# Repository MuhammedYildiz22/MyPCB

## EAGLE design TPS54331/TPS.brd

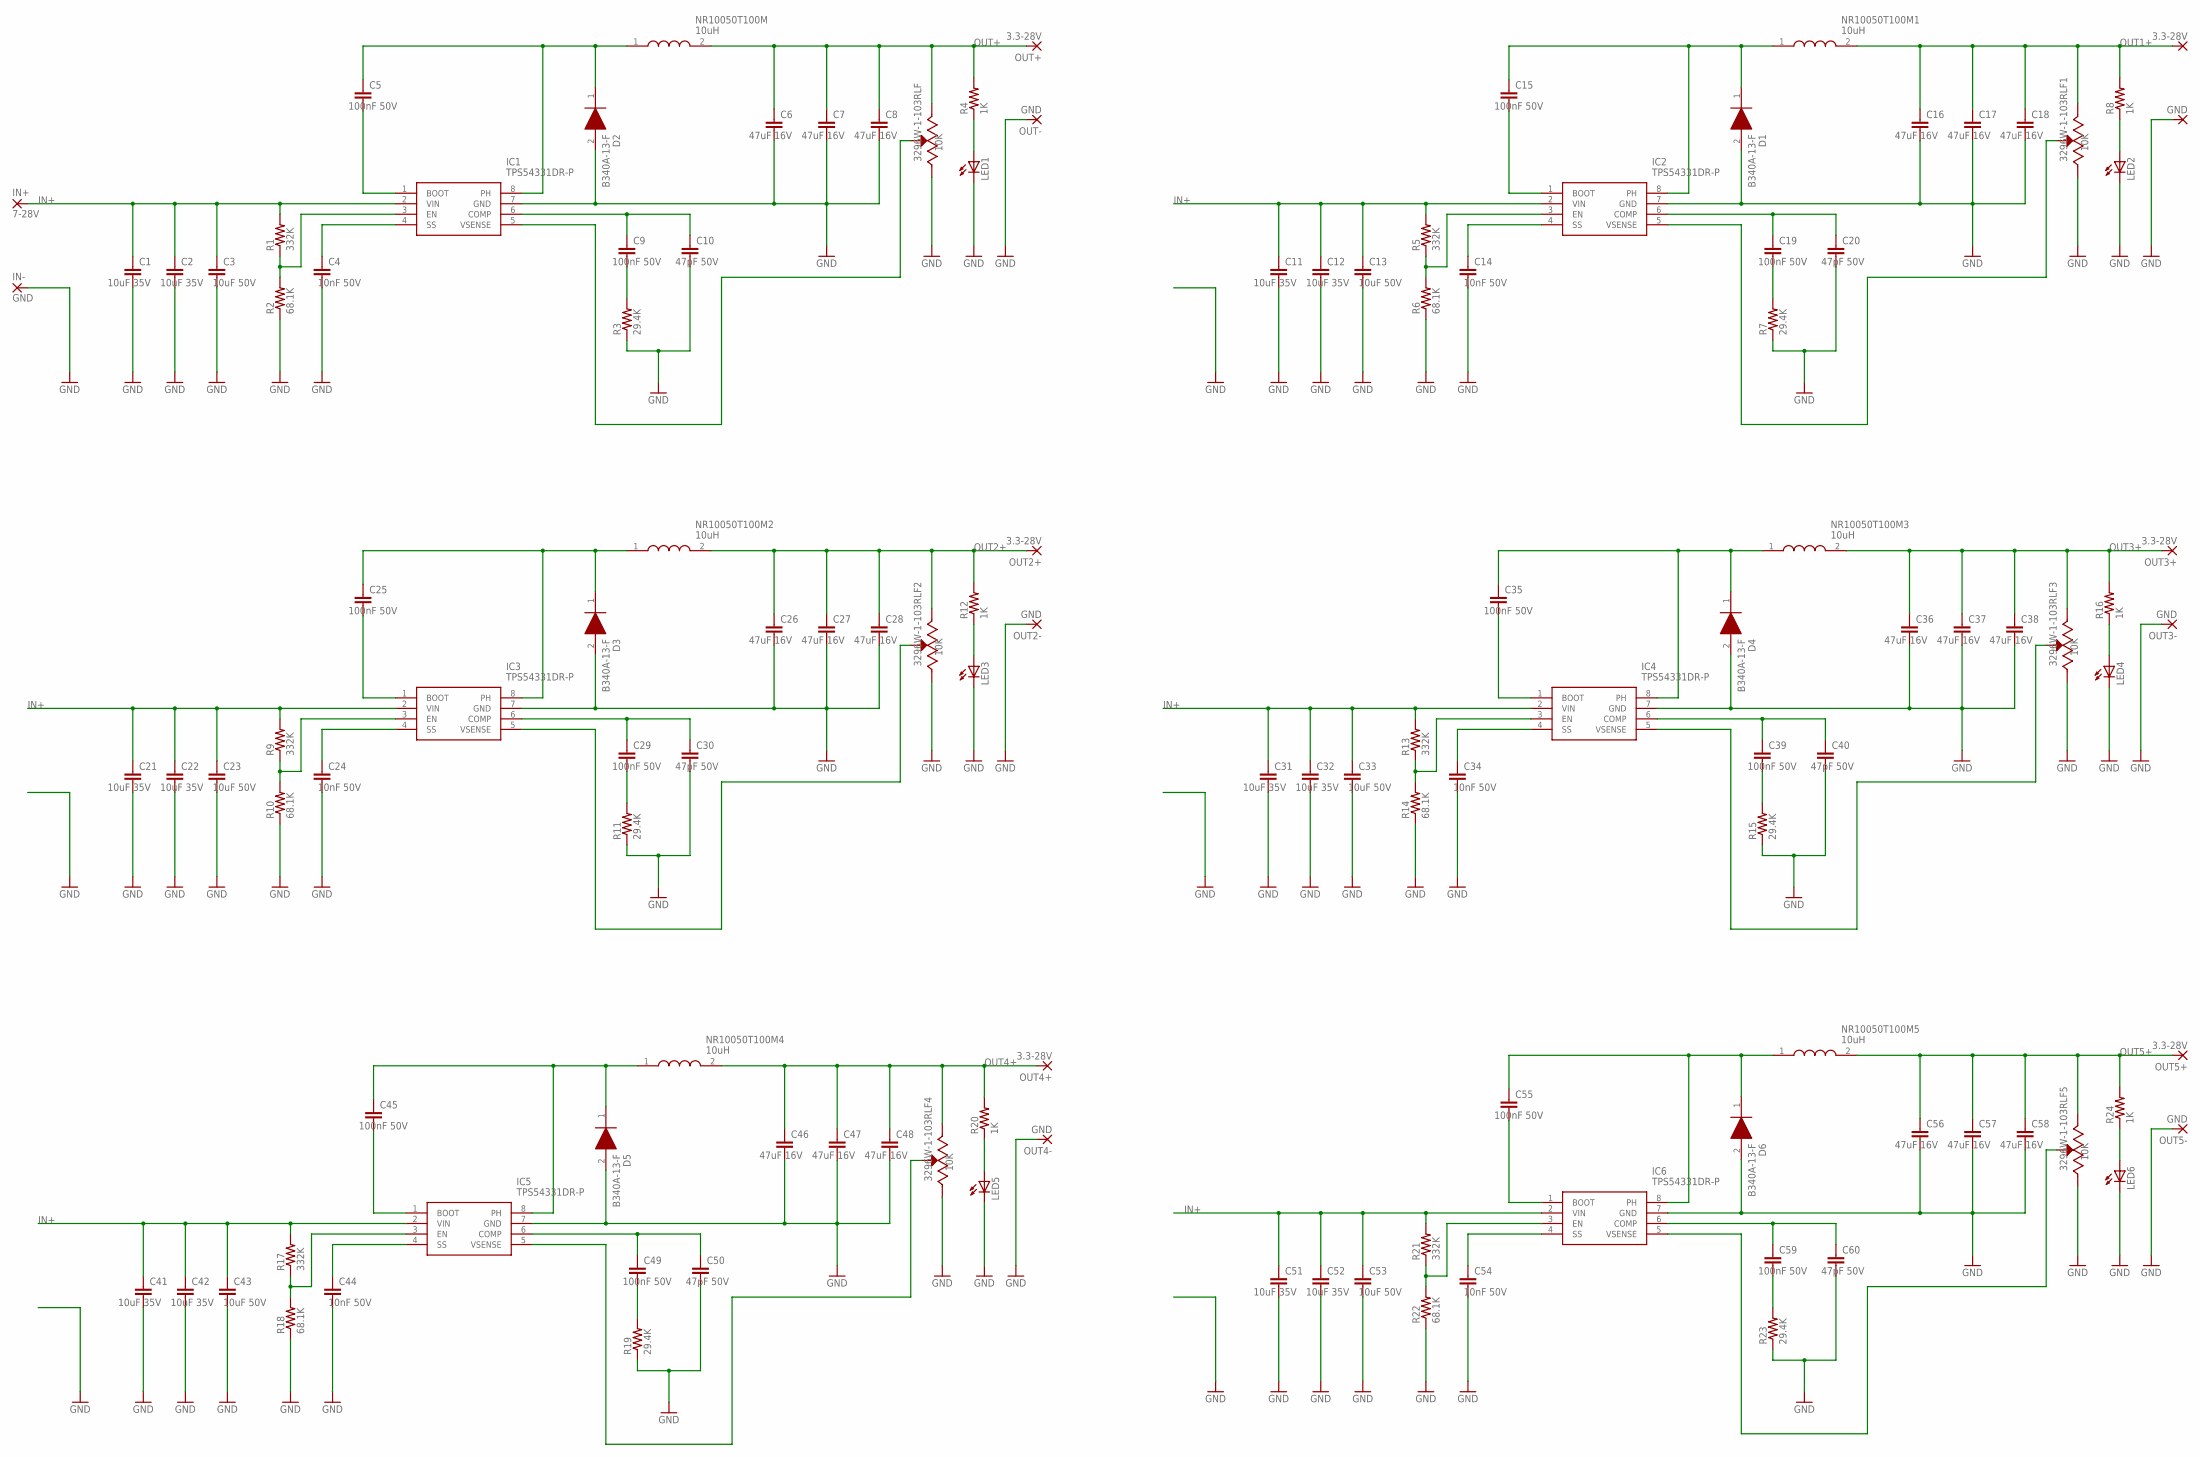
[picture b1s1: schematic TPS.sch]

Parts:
3296W-1-103RLF, 3296W-1-103RLF1, 3296W-1-103RLF2, 3296W-1-103RLF3, 3296W-1-103RLF4, 3296W-1-103RLF5: 10K; TRIM_3296W-1-103RLF
C1, C2, C11, C12, C21, C22, C31, C32, C41, C42, C51, C52: 10uF 35V; SPARKFUN_1206
C3, C13, C23, C33, C43, C53: 10uF 50V; 1206
C4, C14, C24, C34, C44, C54: 10nF 50V; SPARKFUN_1206
C5, C9, C15, C19, C25, C29, C35, C39, C45, C49, C55, C59: 100nF 50V; SPARKFUN_1206
C6, C7, C8, C16, C17, C18, C26, C27, C28, C36, C37, C38, C46, C47, C48, C56, C57, C58: 47uF 16V; SPARKFUN_1206
C10, C20, C30, C40, C50, C60: 47pF 50V; SPARKFUN_1206
D1, D2, D3, D4, D5, D6: B340A-13-F; DIOM5226X240N
IC1, IC2, IC3, IC4, IC5, IC6: TPS54331DR-P; SOIC127P600X175-8N
IN+: 7-28V; 5-2,5
IN-: GND; 3,81/1,4
LED1, LED2, LED3, LED4, LED5, LED6: SPARKFUN_LED1206; SPARKFUN_LED-1206
NR10050T100M, NR10050T100M1, NR10050T100M2, NR10050T100M3, NR10050T100M4, NR10050T100M5: 10uH; NR10050T100M
OUT1+, OUT2+, OUT3+, OUT4+, OUT5+: 3.3-28V; 5-2,5
OUT1-, OUT2-, OUT3-, OUT4-, OUT5-: GND; 3,81/1,4
OUT+: 3.3-28V; 5-2,5
OUT-: GND; 3,81/1,4
R1, R5, R9, R13, R17, R21: 332K; M1206
R2, R6, R10, R14, R18, R22: 68.1K; M1206
R3, R7, R11, R15, R19, R23: 29.4K; M1206
R4, R8, R12, R16, R20, R24: 1K; M1206

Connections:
GND: 3296W-1-103RLF.1 (CCW), 3296W-1-103RLF1.1 (CCW), 3296W-1-103RLF2.1 (CCW), 3296W-1-103RLF3.1 (CCW), 3296W-1-103RLF4.1 (CCW), 3296W-1-103RLF5.1 (CCW), C1.2, C2.2, C3.2, C4.2, C6.2, C7.2, C8.2, C10.2, C11.2, C12.2, C13.2, C14.2, C16.2, C17.2, C18.2, C20.2, C21.2, C22.2, C23.2, C24.2, C26.2, C27.2, C28.2, C30.2, C31.2, C32.2, C33.2, C34.2, C36.2, C37.2, C38.2, C40.2, C41.2, C42.2, C43.2, C44.2, C46.2, C47.2, C48.2, C50.2, C51.2, C52.2, C53.2, C54.2, C56.2, C57.2, C58.2, C60.2, D1.2 (A), D2.2 (A), D3.2 (A), D4.2 (A), D5.2 (A), D6.2 (A), IC1.7 (GND), IC2.7 (GND), IC3.7 (GND), IC4.7 (GND), IC5.7 (GND), IC6.7 (GND), IN-.1, LED1.C, LED2.C, LED3.C, LED4.C, LED5.C, LED6.C, OUT1-.1, OUT2-.1, OUT3-.1, OUT4-.1, OUT5-.1, OUT-.1, R2.1, R3.1, R6.1, R7.1, R10.1, R11.1, R14.1, R15.1, R18.1, R19.1, R22.1, R23.1
IN+: C1.1, C2.1, C3.1, C11.1, C12.1, C13.1, C21.1, C22.1, C23.1, C31.1, C32.1, C33.1, C41.1, C42.1, C43.1, C51.1, C52.1, C53.1, IC1.2 (VIN), IC2.2 (VIN), IC3.2 (VIN), IC4.2 (VIN), IC5.2 (VIN), IC6.2 (VIN), IN+.1, R1.2, R5.2, R9.2, R13.2, R17.2, R21.2
unnamed: IC1.3 (EN), R1.1, R2.2
unnamed: C4.1, IC1.4 (SS)
unnamed: C5.2, IC1.1 (BOOT)
unnamed: C5.1, D2.1 (K), IC1.8 (PH), NR10050T100M.1
unnamed: C9.1, C10.1, IC1.6 (COMP)
unnamed: C9.2, R3.2
unnamed: IC2.3 (EN), R5.1, R6.2
unnamed: LED1.A, R4.1
unnamed: 3296W-1-103RLF.2 (WIPER), IC1.5 (VSENSE)
unnamed: C14.1, IC2.4 (SS)
unnamed: C15.2, IC2.1 (BOOT)
unnamed: C15.1, D1.1 (K), IC2.8 (PH), NR10050T100M1.1
unnamed: C19.1, C20.1, IC2.6 (COMP)
unnamed: C19.2, R7.2
unnamed: LED2.A, R8.1
unnamed: 3296W-1-103RLF1.2 (WIPER), IC2.5 (VSENSE)
unnamed: IC3.3 (EN), R9.1, R10.2
unnamed: C24.1, IC3.4 (SS)
unnamed: C25.2, IC3.1 (BOOT)
unnamed: C25.1, D3.1 (K), IC3.8 (PH), NR10050T100M2.1
unnamed: C29.1, C30.1, IC3.6 (COMP)
unnamed: C29.2, R11.2
unnamed: LED3.A, R12.1
unnamed: 3296W-1-103RLF2.2 (WIPER), IC3.5 (VSENSE)
unnamed: IC4.3 (EN), R13.1, R14.2
unnamed: C34.1, IC4.4 (SS)
unnamed: C35.2, IC4.1 (BOOT)
unnamed: C35.1, D4.1 (K), IC4.8 (PH), NR10050T100M3.1
unnamed: C39.1, C40.1, IC4.6 (COMP)
unnamed: C39.2, R15.2
unnamed: LED4.A, R16.1
unnamed: 3296W-1-103RLF3.2 (WIPER), IC4.5 (VSENSE)
unnamed: IC5.3 (EN), R17.1, R18.2
unnamed: C44.1, IC5.4 (SS)
unnamed: C45.2, IC5.1 (BOOT)
unnamed: C45.1, D5.1 (K), IC5.8 (PH), NR10050T100M4.1
unnamed: C49.1, C50.1, IC5.6 (COMP)
unnamed: C49.2, R19.2
unnamed: LED5.A, R20.1
unnamed: 3296W-1-103RLF4.2 (WIPER), IC5.5 (VSENSE)
unnamed: IC6.3 (EN), R21.1, R22.2
unnamed: C54.1, IC6.4 (SS)
unnamed: C55.2, IC6.1 (BOOT)
unnamed: C55.1, D6.1 (K), IC6.8 (PH), NR10050T100M5.1
unnamed: C59.1, C60.1, IC6.6 (COMP)
unnamed: C59.2, R23.2
unnamed: LED6.A, R24.1
unnamed: 3296W-1-103RLF5.2 (WIPER), IC6.5 (VSENSE)
OUT1+: 3296W-1-103RLF1.3 (CW), C16.1, C17.1, C18.1, NR10050T100M1.2, OUT1+.1, R8.2
OUT2+: 3296W-1-103RLF2.3 (CW), C26.1, C27.1, C28.1, NR10050T100M2.2, OUT2+.1, R12.2
OUT3+: 3296W-1-103RLF3.3 (CW), C36.1, C37.1, C38.1, NR10050T100M3.2, OUT3+.1, R16.2
OUT4+: 3296W-1-103RLF4.3 (CW), C46.1, C47.1, C48.1, NR10050T100M4.2, OUT4+.1, R20.2
OUT5+: 3296W-1-103RLF5.3 (CW), C56.1, C57.1, C58.1, NR10050T100M5.2, OUT5+.1, R24.2
OUT+: 3296W-1-103RLF.3 (CW), C6.1, C7.1, C8.1, NR10050T100M.2, OUT+.1, R4.2

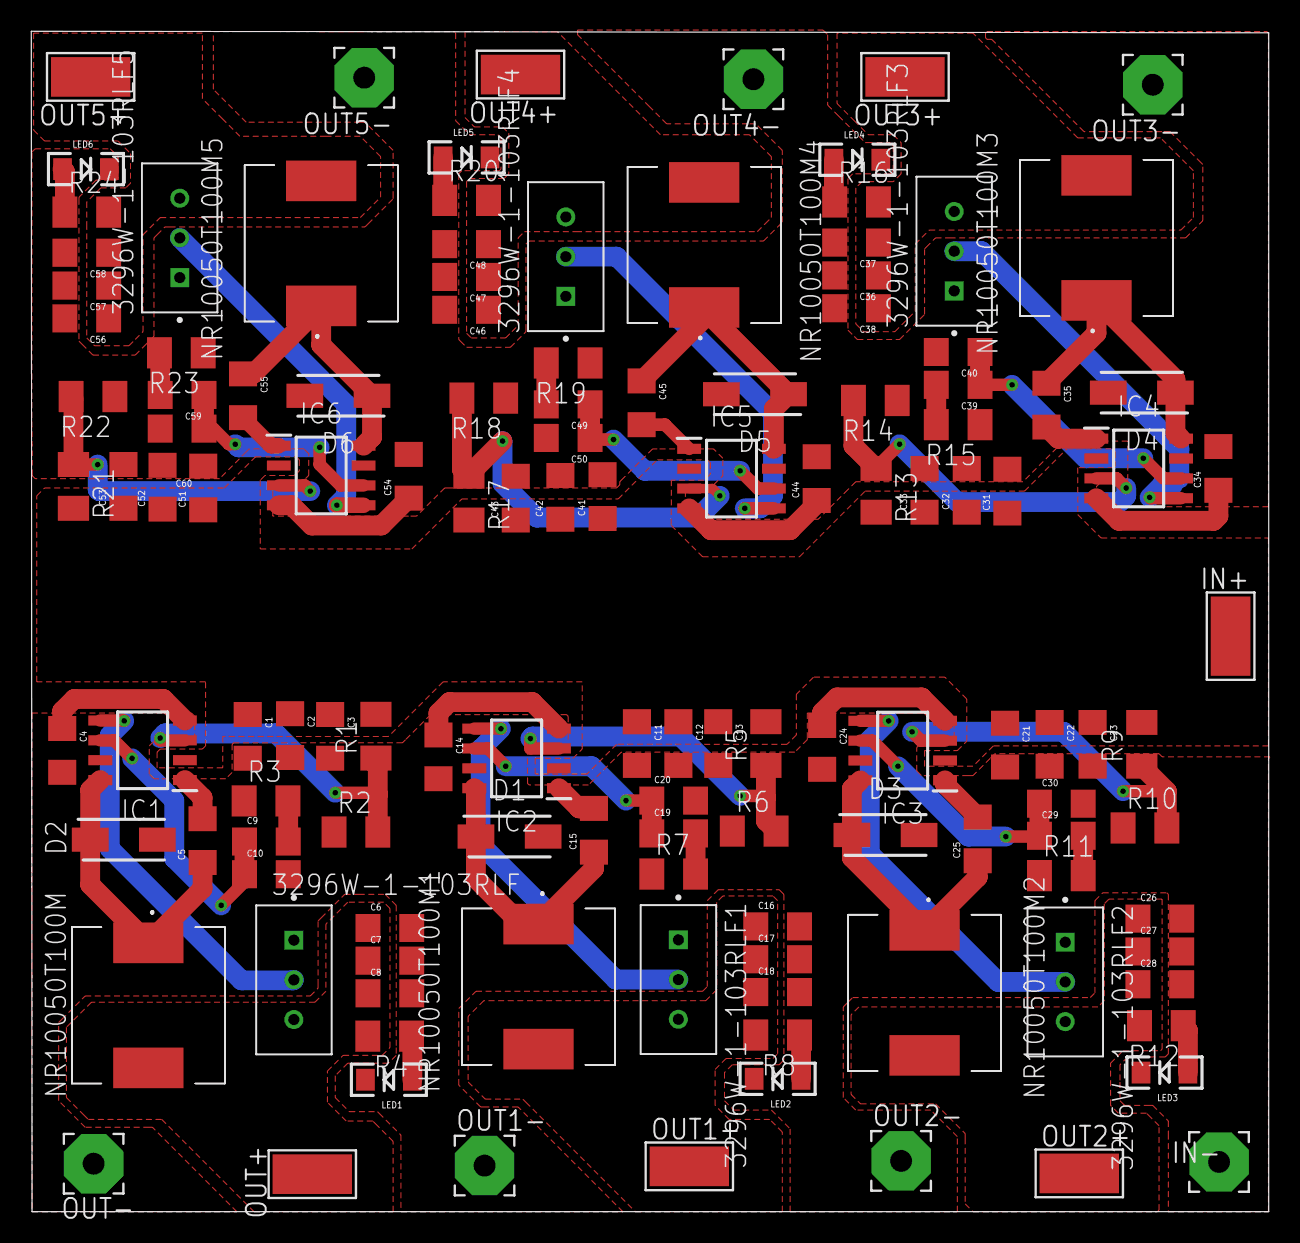
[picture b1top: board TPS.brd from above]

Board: 2 copper layers, 79.2 x 75.5 mm, 128 parts (0 on the bottom side), 56 nets.

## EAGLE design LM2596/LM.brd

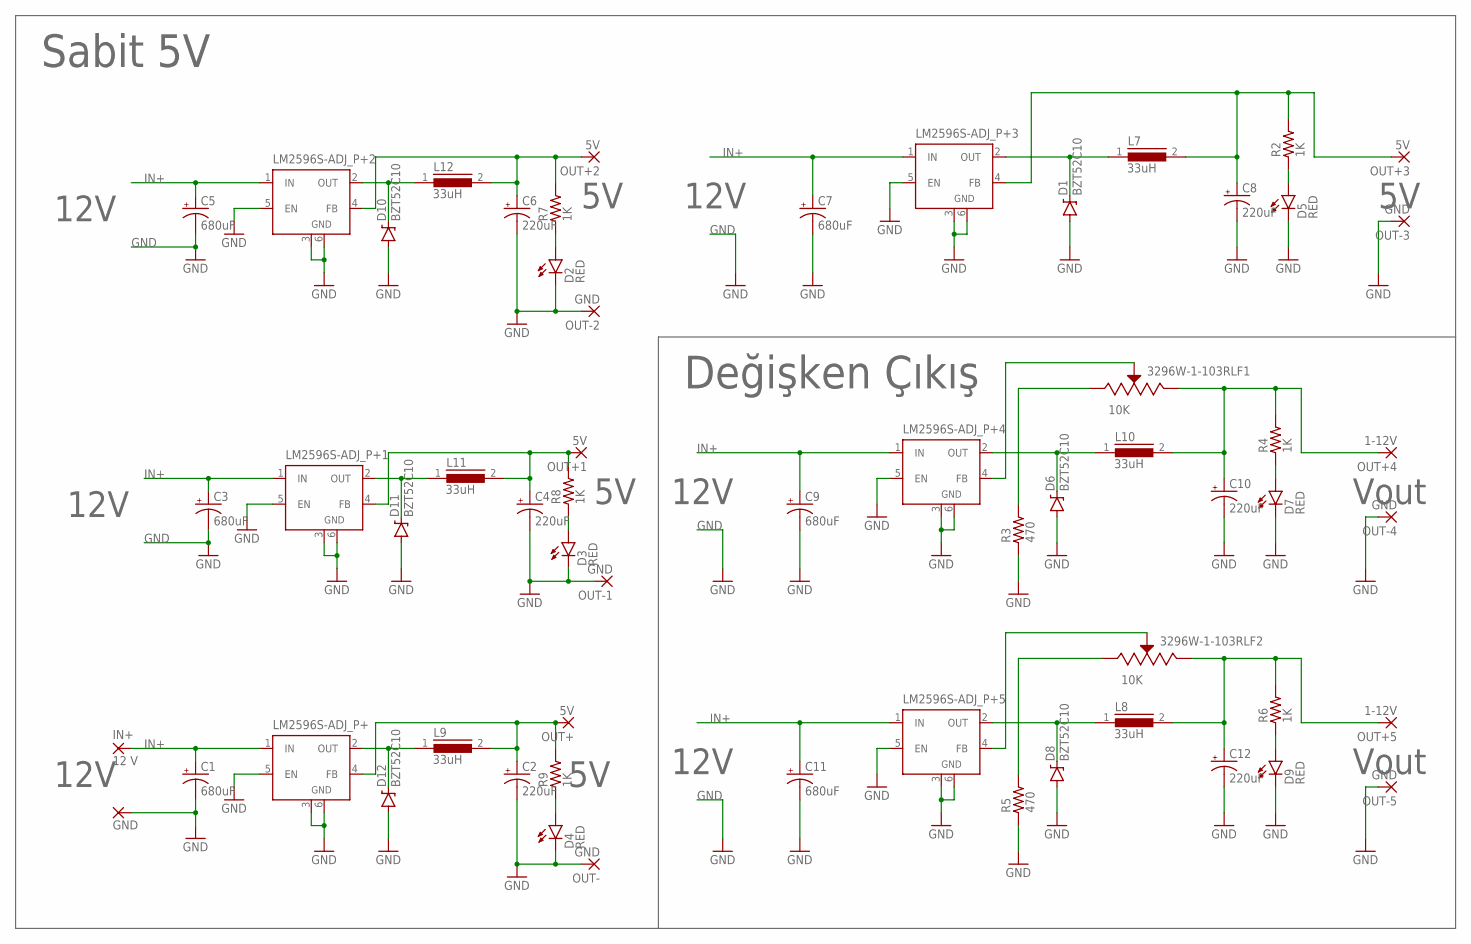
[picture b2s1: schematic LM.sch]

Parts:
3296W-1-103RLF1, 3296W-1-103RLF2: 10K; TRIM_3296W-1-103RLF
C1, C3, C5, C7, C9, C11: 680uF; PANASONIC_G
C2, C4, C6, C8, C10, C12: 220uF; PANASONIC_G
D1, D6, D8, D10, D11, D12: BZT52C10; SOD-123_2
D2, D3, D4, D5, D7, D9: RED; LED-1206
IN+: 12 V; SMD2,54-5,08
IN-: GND; 3,81/1,1
L7, L8, L9, L10, L11, L12: 33uH; DR127
LM2596S-ADJ_P+, LM2596S-ADJ_P+1, LM2596S-ADJ_P+2, LM2596S-ADJ_P+3, LM2596S-ADJ_P+4, LM2596S-ADJ_P+5: LM2596S; TO263-5
OUT+, OUT+1, OUT+2, OUT+3: 5V; SMD2,54-5,08
OUT+4, OUT+5: 1-12V; SMD2,54-5,08
OUT-, OUT-1, OUT-2, OUT-3, OUT-4, OUT-5: GND; 3,81/1,1
R2, R4, R6, R7, R8, R9: 1K; R0805
R3, R5: 470; R1206

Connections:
GND: C1.-, C2.-, C3.-, C4.-, C5.-, C6.-, C7.-, C8.-, C9.-, C10.-, C11.-, C12.-, D1.A, D2.C, D3.C, D4.C, D5.C, D6.A, D7.C, D8.A, D9.C, D10.A, D11.A, D12.A, IN-.1, LM2596S-ADJ_P+.3 (GND), LM2596S-ADJ_P+.5 (EN), LM2596S-ADJ_P+.6 (GND), LM2596S-ADJ_P+1.3 (GND), LM2596S-ADJ_P+1.5 (EN), LM2596S-ADJ_P+1.6 (GND), LM2596S-ADJ_P+2.3 (GND), LM2596S-ADJ_P+2.5 (EN), LM2596S-ADJ_P+2.6 (GND), LM2596S-ADJ_P+3.3 (GND), LM2596S-ADJ_P+3.5 (EN), LM2596S-ADJ_P+3.6 (GND), LM2596S-ADJ_P+4.3 (GND), LM2596S-ADJ_P+4.5 (EN), LM2596S-ADJ_P+4.6 (GND), LM2596S-ADJ_P+5.3 (GND), LM2596S-ADJ_P+5.5 (EN), LM2596S-ADJ_P+5.6 (GND), OUT-.1, OUT-1.1, OUT-2.1, OUT-3.1, OUT-4.1, OUT-5.1, R3.1, R5.1
IN+: C1.+, C3.+, C5.+, C7.+, C9.+, C11.+, IN+.1, LM2596S-ADJ_P+.1 (IN), LM2596S-ADJ_P+1.1 (IN), LM2596S-ADJ_P+2.1 (IN), LM2596S-ADJ_P+3.1 (IN), LM2596S-ADJ_P+4.1 (IN), LM2596S-ADJ_P+5.1 (IN)
unnamed: D4.A, R9.1
unnamed: D12.C, L9.1, LM2596S-ADJ_P+.2 (OUT)
unnamed: C2.+, L9.2, LM2596S-ADJ_P+.4 (FB), OUT+.1, R9.2
unnamed: D3.A, R8.1
unnamed: D11.C, L11.1, LM2596S-ADJ_P+1.2 (OUT)
unnamed: C4.+, L11.2, LM2596S-ADJ_P+1.4 (FB), OUT+1.1, R8.2
unnamed: D2.A, R7.1
unnamed: D10.C, L12.1, LM2596S-ADJ_P+2.2 (OUT)
unnamed: C6.+, L12.2, LM2596S-ADJ_P+2.4 (FB), OUT+2.1, R7.2
unnamed: D1.C, L7.1, LM2596S-ADJ_P+3.2 (OUT)
unnamed: C8.+, L7.2, LM2596S-ADJ_P+3.4 (FB), OUT+3.1, R2.2
unnamed: D5.A, R2.1
unnamed: D6.C, L10.1, LM2596S-ADJ_P+4.2 (OUT)
unnamed: 3296W-1-103RLF1.3 (CW), C10.+, L10.2, OUT+4.1, R4.2
unnamed: 3296W-1-103RLF1.1 (CCW), R3.2
unnamed: D7.A, R4.1
unnamed: D8.C, L8.1, LM2596S-ADJ_P+5.2 (OUT)
unnamed: 3296W-1-103RLF2.3 (CW), C12.+, L8.2, OUT+5.1, R6.2
unnamed: 3296W-1-103RLF2.1 (CCW), R5.2
unnamed: D9.A, R6.1
unnamed: 3296W-1-103RLF1.2 (WIPER), LM2596S-ADJ_P+4.4 (FB)
unnamed: 3296W-1-103RLF2.2 (WIPER), LM2596S-ADJ_P+5.4 (FB)

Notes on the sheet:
12V
Vout
Sabit 5V
Değişken Çıkış

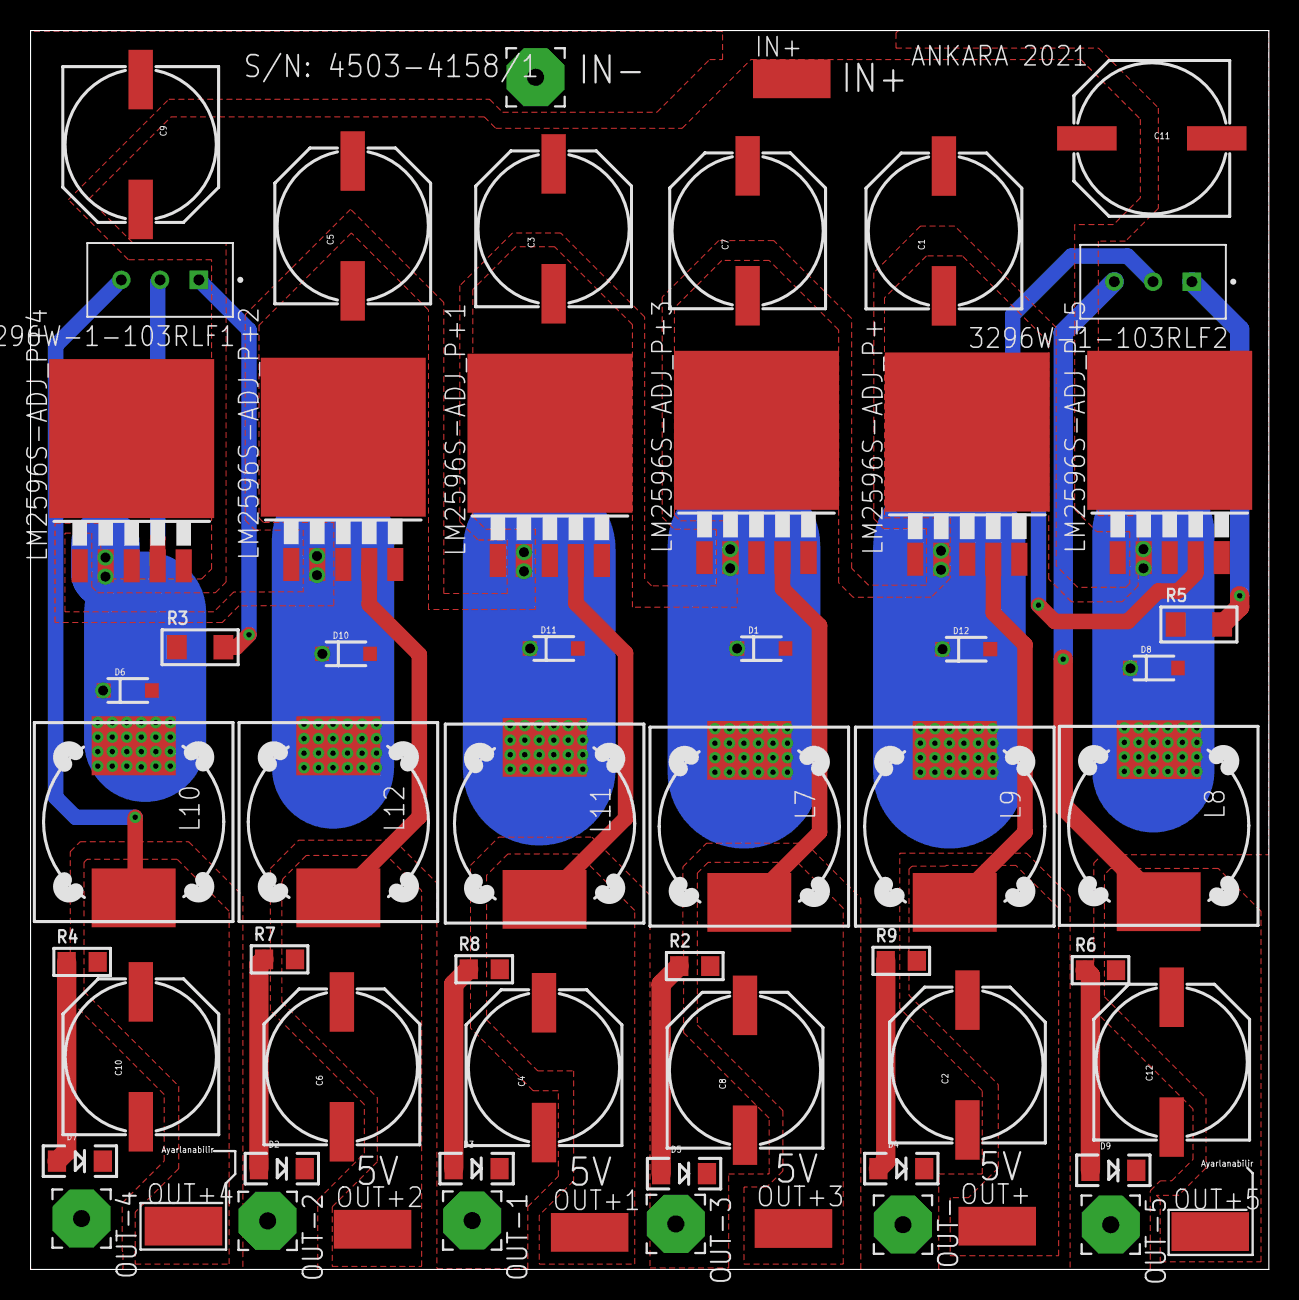
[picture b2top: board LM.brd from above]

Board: 2 copper layers, 81.1 x 81.1 mm, 60 parts (0 on the bottom side), 24 nets.

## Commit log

2023-02-27 Create LM5116 DC-DC Convrter

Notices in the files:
parts and their libraries:
cap_master-smd: Copyright (C) 2007, Bob Starr
SparkFun-LED: Licensing: Creative Commons ShareAlike 4.0 International - https://creativecommons.org/licenses/by-sa/4.0
SparkFun: Licensing: CC v3.0 Share-Alike You are welcome to use this library for commercial purposes.
